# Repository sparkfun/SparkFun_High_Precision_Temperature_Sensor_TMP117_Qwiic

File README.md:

SparkFun High Precision Temperature Sensor TMP117 (Qwiic)
========================================

[*SparkFun High Precision Temperature Sensor TMP117 (Qwiic) (SEN-15805)*](https://www.sparkfun.com/products/15805)

The TMP117 is a high precision temperature sensor with accuracy of up to +/-0.1 degrees Celsius (across the temperature range of -20°C to +50°Cs with no calibration) and an operating temperature range of -55°C to +150°C. It is NIST traceable and verified with equipment that is calibrated to ISO/IEC 17025 accredited standards. It has a very low power consumption with a supply range of 1.8V to 5.5V.

The TMP117 address can be changed with an external jumper to 4 different addresses. There are 4 different conversion modes that it can read from, with continuous conversion, shutdown, and one shot conversion. There is also digital offset for system correction, programmable temperature limits, general-purpose EEPROM, and selectable averaging.

Repository Contents
-------------------

* **/Documentation** - Data sheets, additional product information
* **/Hardware** - Eagle design files (.brd, .sch)
* **/Production** - Production panel files (.brd)

Documentation
--------------

* **[Installing an Arduino Library Guide](https://learn.sparkfun.com/tutorials/installing-an-arduino-library)** - Basic information on how to install an Arduino library.
* **[Library](https://github.com/sparkfun/SparkFun_TMP117_Arduino_Library)** - Arduino library for the SparkFun High Precision Temperature Sensor TMP117 (Qwiic).
* **[Hookup Guide](https://learn.sparkfun.com/tutorials/qwiic-tmp117-high-precision-digital-temperature-sensor-hookup-guide)** - Basic hookup guide for the SparkFun High Precision Temperature Sensor TMP117 (Qwiic).

Version History
---------------

* [SparkFun High Precision Temperature Sensor TMP117 (Qwiic)](https://www.sparkfun.com/products/15805) - SparkFun Reds
* [SparkX Qwiic TMP117](https://www.sparkfun.com/products/15413) - Initial product release under SparkX 

License Information
-------------------

This product is _**open source**_! 

Please review the LICENSE.md file for license information. 

If you have any questions or concerns on licensing, please contact technical support on our [SparkFun forums](https://forum.sparkfun.com/viewforum.php?f=152).

Distributed as-is; no warranty is given.

- Your friends at SparkFun.

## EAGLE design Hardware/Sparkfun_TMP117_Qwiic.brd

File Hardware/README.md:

SparkFun High Precision Temperature Sensor TMP117 (Qwiic) Design Files
=====================================

The .sch and .brd files hare are Eagle CAD schematic and PCB design files from SparkFun Electronics.
A freeware version of Eagle can be found [here](http://www.cadsoftusa.com/download-eagle/freeware/).

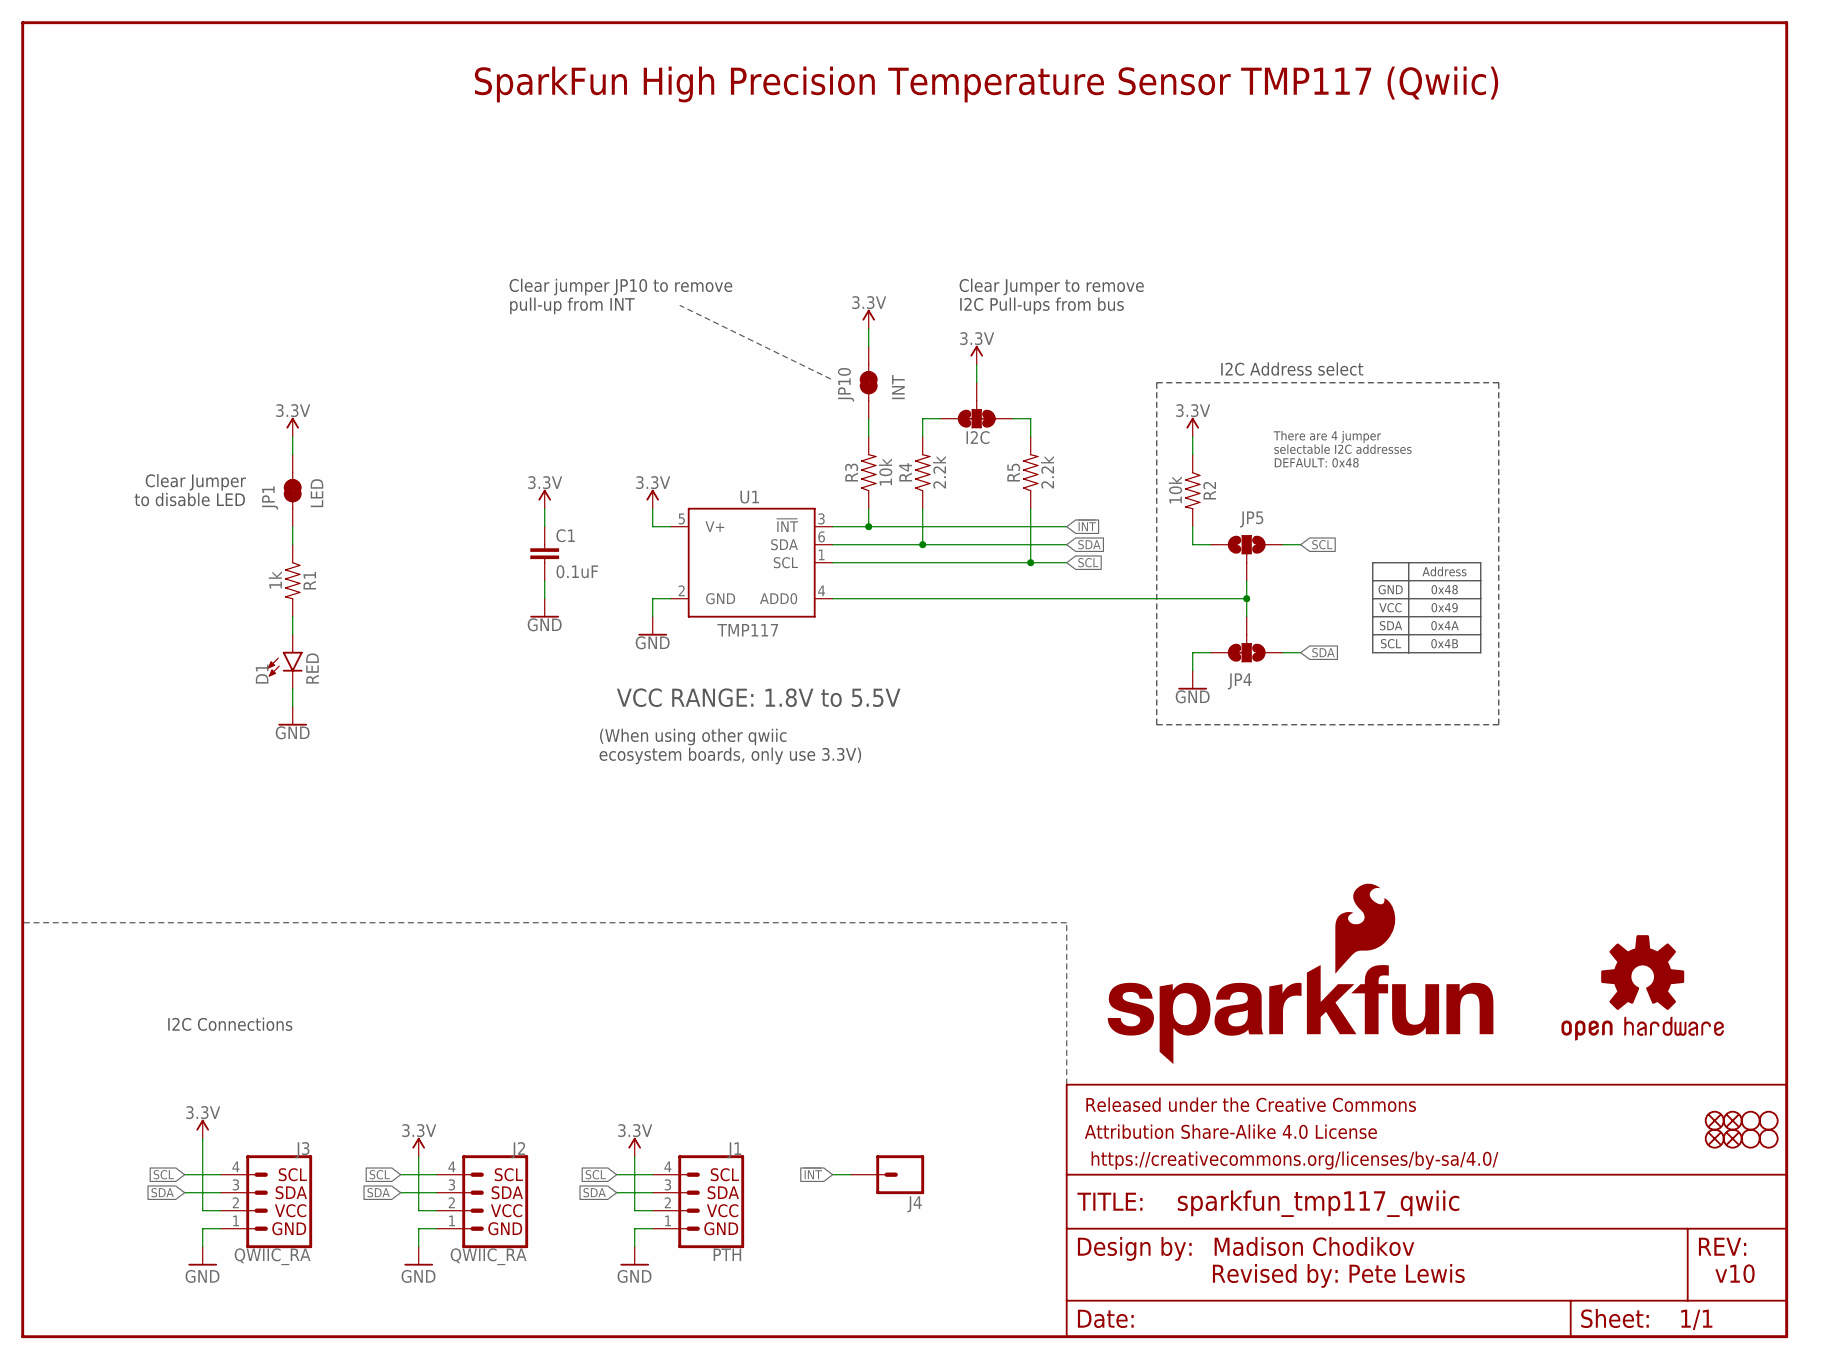
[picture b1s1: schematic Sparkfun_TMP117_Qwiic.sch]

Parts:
C1: 0.1uF; 0603
D1: RED; LED-0603
FD1, FD2, FD3, FD4: FIDUCIALUFIDUCIAL; FIDUCIAL-MICRO
FRAME1: FRAME-LETTER; CREATIVE_COMMONS
I2C: JUMPER-SMT_3_2-NC_TRACE_SILK; SMT-JUMPER_3_2-NC_TRACE_SILK
J1: PTH; 1X04_NO_SILK
J2, J3: QWIIC_RA; JST04_1MM_RA
J4: CONN_01PTH_NO_SILK_YES_STOP; 1X01_NO_SILK
JP1: LED; SMT-JUMPER_2_NC_TRACE_SILK
JP2, JP3, JP8, JP9: STAND-OFF
JP4: JUMPER-SMT_3_1-NC_TRACE_NO-SILK; SMT-JUMPER_3_1-NC_TRACE_NO-SILK
JP5: JUMPER-SMT_3_NO_NO_SILK; SMT-JUMPER_3_0-NO_TRACE_NO-SILK
JP10: INT; SMT-JUMPER_2_NC_TRACE_SILK
LOGO1: OSHW-LOGOMINI; OSHW-LOGO-MINI
LOGO4: SFE_LOGO_NAME_FLAME.1_INCH; SFE_LOGO_NAME_FLAME_.1
R1: 1k; 0603
R2, R3: 10k; 0603
R4, R5: 2.2k; 0603
U1: TMP117

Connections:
3.3V: C1.1, I2C.2, J1.2, J2.2, J3.2, JP1.2, JP10.2, R2.1, U1.5 (V+)
!INT: J4.1, R3.1, U1.3 (!INT)
ADD0: JP4.2, JP5.2, U1.4 (ADD0)
GND: C1.2, D1.C, J1.1, J2.1, J3.1, JP4.3, U1.2 (GND)
unnamed: D1.A, R1.2
unnamed: I2C.1, R5.2
unnamed: I2C.3, R4.2
unnamed: JP10.1, R3.2
unnamed: JP5.1, R2.2
unnamed: JP1.1, R1.1
SCL: J1.4, J2.4, J3.4, JP5.3, R5.1, U1.1 (SCL)
SDA: J1.3, J2.3, J3.3, JP4.1, R4.1, U1.6 (SDA)

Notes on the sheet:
I2C Connections
SparkFun High Precision Temperature Sensor TMP117 (Qwiic)
Madison Chodikov
Clear Jumper to remove I2C Pull-ups from bus
Clear jumper JP10 to remove pull-up from INT
v10
There are 4 jumper selectable I2C addresses DEFAULT: 0x48
Address
0x48
0x49
0x4A
0x4B
GND
VCC
SDA
SCL
I2C Address select
Clear Jumper to disable LED
Revised by: Pete Lewis
VCC RANGE: 1.8V to 5.5V
(When using other qwiic ecosystem boards, only use 3.3V)

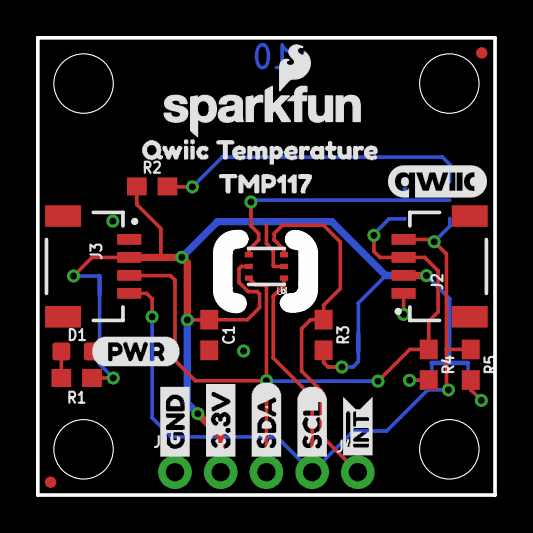
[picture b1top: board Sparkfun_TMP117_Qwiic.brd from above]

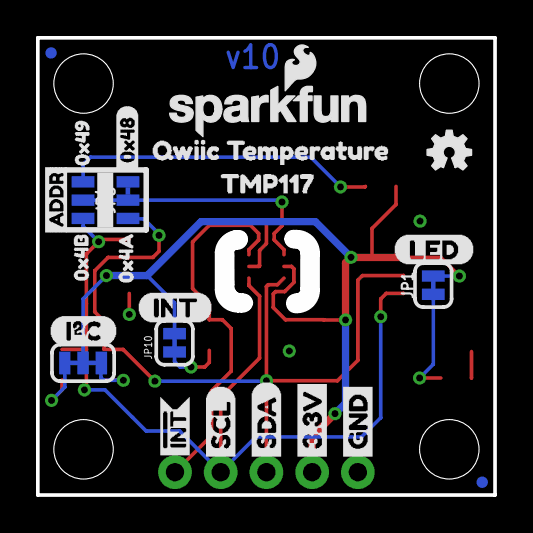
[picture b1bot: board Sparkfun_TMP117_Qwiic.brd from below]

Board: 2 copper layers, 25.4 x 25.4 mm, 53 parts (24 on the bottom side), 12 nets.

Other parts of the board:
LOGO2: SFE_LOGO_NAME_FLAME.1_INCH; SFE_LOGO_NAME_FLAME_.1
U$1, U$6: QWIIC_TEMPERATURE2
U$2: 0X491
U$3, U$11: INT#-[<-04
U$4, U$5: TMP1171
U$7: INT-()-04
U$8: LED0
U$9, U$12: SCL-[)
U$10, U$23: GND-04
U$13, U$14: SDA-[)
U$15: QWIIC_5.5MM
U$16: 0X4A2
U$17: 0X4B3
U$18: ADDR0
U$19, U$22: 3.3V
U$20: PWR-()-04
U$21: I_SUPER2_C-()-04
U$42: 0X480

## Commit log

2019-10-17 initial commit - eagle changes too
    Changes to eagle files:
    -Adjusted dimensions and layout to 1"x1" (SPX version was .95"x.95")
    -SparkFun logo
    -Added version number
    -Added measures
2019-10-17 more layout changes
    -moved to 4 jumpers on address select, to fully remove pull resisor when you cut trace. Previous version had pull down resistor permenantly in circuit, so it would be tied to SDA or SCL when those ad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
    -SCH cleanup
    -rerouting as necessary.
    -added LED bypass jumper
2019-10-21 post design review changes
    -Added fiducials
    -added bottom two standoffs
    -switched to SFE logo with flame
    -moved I2C jumper to bottom
    -added outer box silk to address jumpers
    -moved pwr LED and jumper to make room for standoff
2019-10-21 parts to SFE libraries
2019-10-21 1st run of checklist
    -version font type in schematic
    -silk width bumped up to 8 mils on a couple jumpers and the tmp117 package
2019-10-21 checklist catches
    -remove package value on jumpers (SCH)
    -added VCC range text obj
    -fixed drc errors cause by unconnected dimension wires on special route out stuff near IC
2019-11-14 Update image and links in readme

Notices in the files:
parts and their libraries:
SparkFun-Capacitors: Licensing: Creative Commons ShareAlike 4.0 International - https://creativecommons.org/licenses/by-sa/4.0
SparkFun-Aesthetics: Released under the Creative Commons Attribution Share-Alike 4.0 License
SparkFun-Aesthetics: https://creativecommons.org/licenses/by-sa/4.0
